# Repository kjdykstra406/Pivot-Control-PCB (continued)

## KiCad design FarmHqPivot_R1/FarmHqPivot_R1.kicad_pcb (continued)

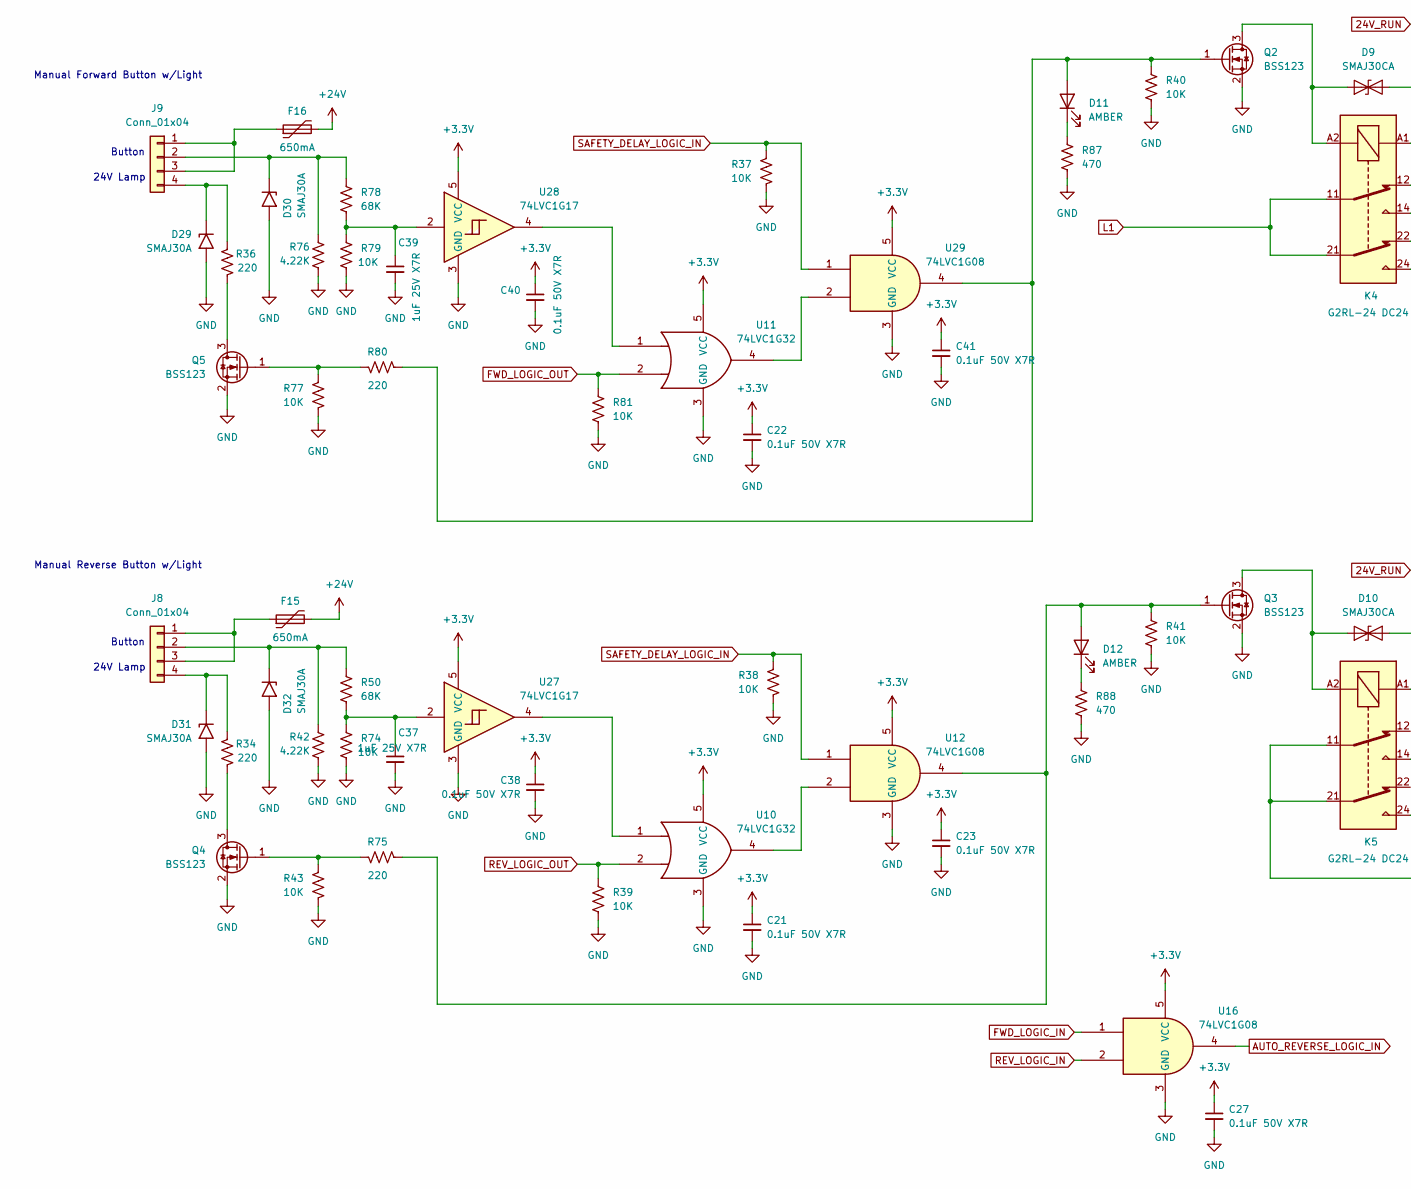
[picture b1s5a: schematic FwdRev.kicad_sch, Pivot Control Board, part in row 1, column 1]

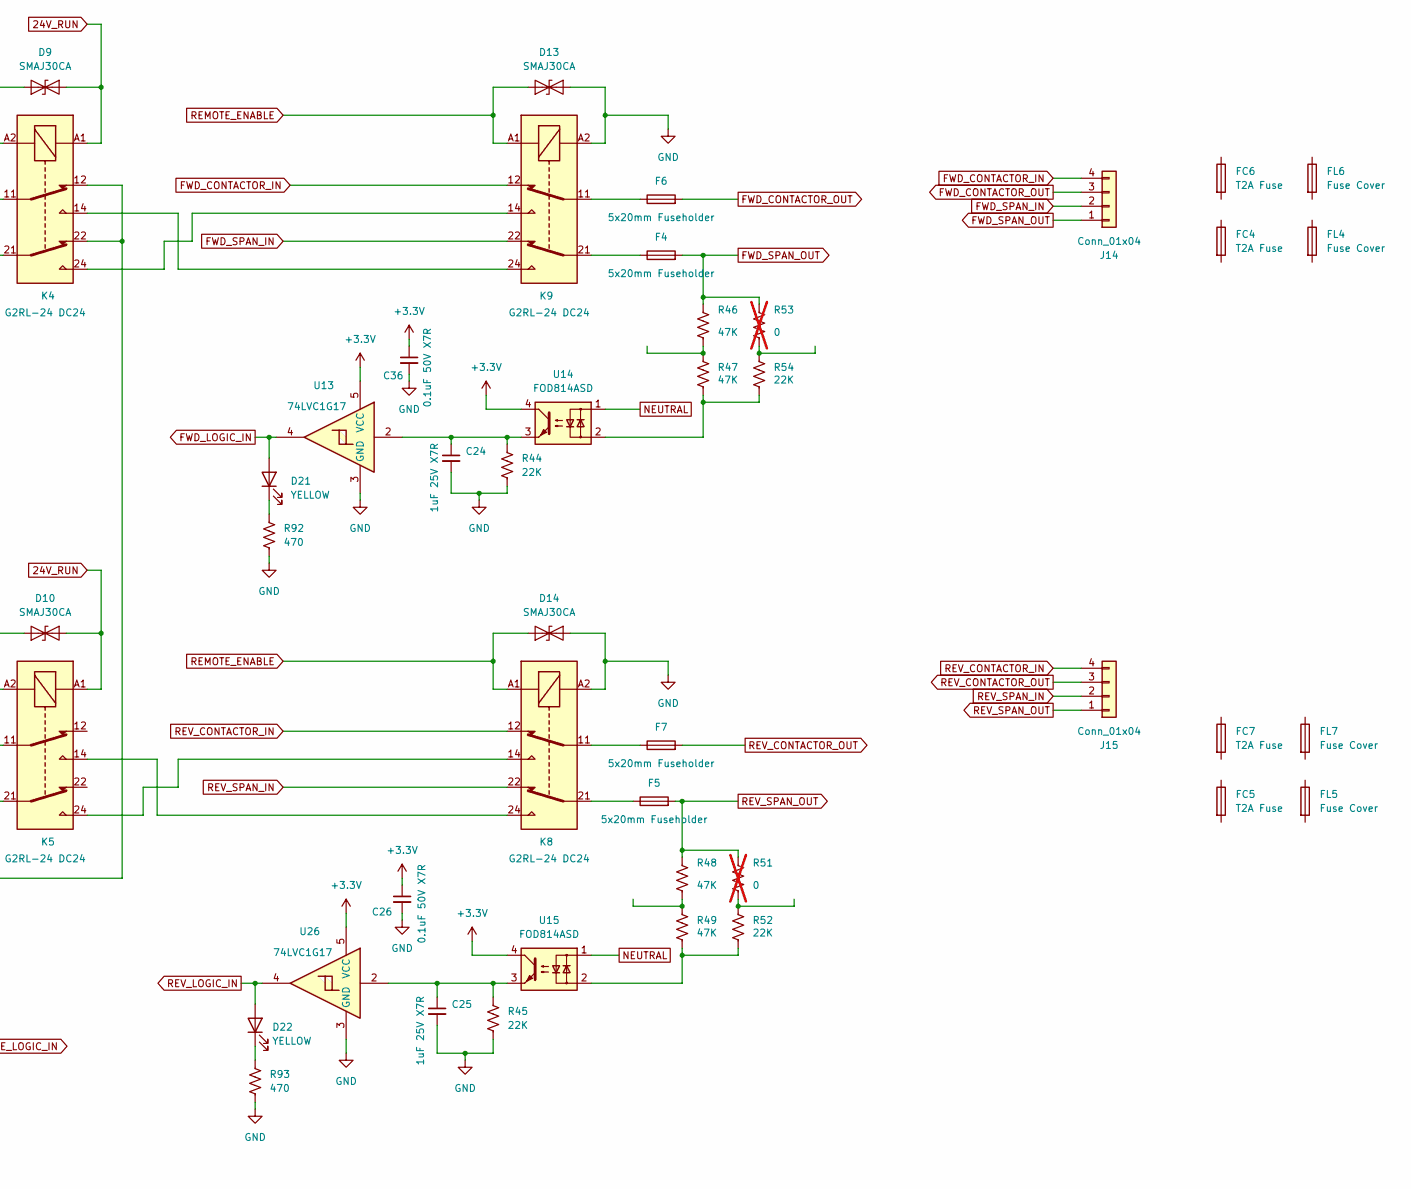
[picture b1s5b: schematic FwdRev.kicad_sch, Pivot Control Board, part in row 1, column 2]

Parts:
C21, C22, C23, C26, C27, C36, C38, C40, C41: 0.1uF 50V X7R; C_0603_1608Metric; Digikey 399-C0603C104K5RACTUDKR-ND
C24, C25, C37, C39: 1uF 25V X7R; C_0603_1608Metric; Digikey 399-C0603C105K3RACTUDKR-ND
D9, D10, D13, D14: SMAJ30CA; D_SMA; Manufacturer PN SMAJ30CA; Digikey SMAJ30CALFDKR-ND
D11, D12: AMBER; LED_0603_1608Metric; Manufacturer PN 5991030147F; Digikey 350-5991030147FDKR-ND
D21, D22: YELLOW; LED_0603_1608Metric; Manufacturer PN 5991040147F; Digikey 350-5991040147FDKR-ND
D29, D30, D31, D32: SMAJ30A; D_SMA; Manufacturer PN SMAJ30A; Digikey SMAJ30ALFDKR-ND
F4, F5, F6, F7: 5x20mm Fuseholder; 696105003002; Manufacturer PN 696105003002; Digikey 732-11373-ND
F15, F16: 650mA; Fuse_Bourns_MF-RHT100; Manufacturer PN MF-R065; Digikey MF-R065-ND
FC4, FC5, FC6, FC7: T2A Fuse; Manufacturer PN 5HT 2-R; Digikey 5923-5HT2-R-ND
FL4, FL5, FL6, FL7: Fuse Cover; Manufacturer PN 696122003001; Digikey 732-11379-ND
J8, J9: Conn_01x04; TerminalBlock_Phoenix_PT-1,5-4-3.5-H_1x04_P3.50mm_Horizontal; Manufacturer PN 1984633; Digikey 277-1860-ND
J14, J15: Conn_01x04; TerminalBlock_Phoenix_PT-1,5-4-5.0-H_1x04_P5.00mm_Horizontal; Manufacturer PN 1935187; Digikey 277-1579-ND
K4, K5, K8, K9: G2RL-24 DC24; Relay_DPDT_Finder_40.52; Manufacturer PN G2RL-24 DC24; Digikey Z148-ND
Q2, Q3, Q4, Q5: BSS123; SOT-23; Manufacturer PN BSS123; Digikey BSS123NDKR-ND
R34, R36: 220; R_1206_3216Metric; Digikey A130530DKR-ND
R37, R38, R39, R40, R41, R43, R74, R77, R79, R81: 10K; R_0603_1608Metric; Digikey 311-10KLDDKR-ND
R42, R76: 4.22K; R_2010_5025Metric; Digikey 541-4.22KACDKR-ND
R44, R45: 22K; R_0603_1608Metric; Digikey 13-RC0603FR-1322KLDKR-ND
R46, R47, R48, R49: 47K; R_2010_5025Metric; Digikey A130680DKR-ND
R50, R78: 68K; R_0603_1608Metric; Digikey 311-68.0KHRDKR-ND
R51, R53: 0; R_2010_5025Metric; Digikey YAG3380DKR-ND; not fitted
R52, R54: 22K; R_2512_6332Metric; Digikey YAG5925DKR-ND
R75, R80: 220; R_0603_1608Metric; Digikey 311-220HRDKR-ND
R87, R88, R92, R93: 470; R_0603_1608Metric; Digikey 311-470HRDKR-ND
U10, U11: 74LVC1G32; SOT-23-5; Manufacturer PN SN74LVC1G32QDBVRQ1; Digikey 296-24202-6-ND
U12, U16, U29: 74LVC1G08; SOT-23-5; Manufacturer PN SN74LVC1G08DBVR; Digikey 296-11601-6-ND
U13, U26, U27, U28: 74LVC1G17; SOT-23-5; Manufacturer PN SN74LVC1G17DBVR; Digikey 296-11933-6-ND
U14, U15: FOD814ASD; Manufacturer PN FOD814ASD; Digikey FOD814ASDDKR-ND

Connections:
24V_RUN: D9.2 (A2), D10.2 (A2), K4.A1, K5.A1; also elsewhere on the board
+3.3V: C21.1, C22.1, C23.1, C26.1, C27.1, C36.1, C38.1, C40.1, C41.1, U10.5 (VCC), U11.5 (VCC), U12.5 (VCC), U13.5 (VCC), U14.4, U15.4, U16.5 (VCC), U26.5 (VCC), U27.5 (VCC), U28.5 (VCC), U29.5 (VCC); also elsewhere on the board
+24V: F15.2, F16.2; also elsewhere on the board
AUTO_REVERSE_LOGIC_IN: U16.4; also elsewhere on the board
FWD_CONTACTOR_IN: J14.4, K9.12
FWD_CONTACTOR_OUT: F6.2, J14.3
FWD_LOGIC_IN: D21.2 (A), U13.4, U16.1; also elsewhere on the board
FWD_LOGIC_OUT: R81.1, U11.2; also elsewhere on the board
FWD_SPAN_IN: J14.2, K9.22
FWD_SPAN_OUT: F4.2, J14.1, R46.1, R53.1
GND: C21.2, C22.2, C23.2, C24.2, C25.2, C26.2, C27.2, C36.2, C37.2, C38.2, C39.2, C40.2, C41.2, D13.2 (A2), D14.2 (A2), D29.2 (A2), D30.2 (A2), D31.2 (A2), D32.2 (A2), K8.A2, K9.A2, Q2.2 (S), Q3.2 (S), Q4.2 (S), Q5.2 (S), R37.2, R38.2, R39.2, R40.2, R41.2, R42.2, R43.2, R44.2, R45.2, R74.2, R76.2, R77.2, R79.2, R81.2, R87.2, R88.2, R92.2, R93.2, U10.3 (GND), U11.3 (GND), U12.3 (GND), U13.3 (GND), U16.3 (GND), U26.3 (GND), U27.3 (GND), U28.3 (GND), U29.3 (GND); also elsewhere on the board
L1: K4.11, K4.21; also elsewhere on the board
NEUTRAL: U14.1, U15.1; also elsewhere on the board
unnamed: C24.1, R44.1, U13.2, U14.3
unnamed: C25.1, R45.1, U15.3, U26.2
unnamed: C37.1, R50.2, R74.1, U27.2
unnamed: C39.1, R78.2, R79.1, U28.2
unnamed: D9.1 (A1), K4.A2, Q2.3 (D)
unnamed: D10.1 (A1), K5.A2, Q3.3 (D)
unnamed: D11.2 (A), Q2.1 (G), R40.1, R80.2, U29.4
unnamed: D11.1 (K), R87.1
unnamed: D12.2 (A), Q3.1 (G), R41.1, R75.2, U12.4
unnamed: D12.1 (K), R88.1
unnamed: D21.1 (K), R92.1
unnamed: D22.1 (K), R93.1
unnamed: D29.1 (A1), J9.4, R36.1
unnamed: D30.1 (A1), J9.2, R76.1, R78.1
unnamed: D31.1 (A1), J8.4, R34.1
unnamed: D32.1 (A1), J8.2, R42.1, R50.1
unnamed: F4.1, K9.21
unnamed: F5.1, K8.21
unnamed: F6.1, K9.11
unnamed: F7.1, K8.11
unnamed: F15.1, J8.1, J8.3
unnamed: F16.1, J9.1, J9.3
unnamed: K4.12, K4.22, K5.11, K5.21
unnamed: K4.14, K9.24
unnamed: K4.24, K9.14
unnamed: K5.14, K8.24
unnamed: K5.24, K8.14
unnamed: Q4.3 (D), R34.2
unnamed: Q4.1 (G), R43.1, R75.1
unnamed: Q5.3 (D), R36.2
unnamed: Q5.1 (G), R77.1, R80.1
unnamed: R46.2, R47.1
unnamed: R47.2, R54.2, U14.2
unnamed: R48.2, R49.1
unnamed: R49.2, R52.2, U15.2
unnamed: R51.2, R52.1
unnamed: R53.2, R54.1
unnamed: U10.1, U27.4
unnamed: U10.4, U12.2
unnamed: U11.1, U28.4
unnamed: U11.4, U29.2
REMOTE_ENABLE: D13.1 (A1), D14.1 (A1), K8.A1, K9.A1; also elsewhere on the board
REV_CONTACTOR_IN: J15.4, K8.12
REV_CONTACTOR_OUT: F7.2, J15.3
REV_LOGIC_IN: D22.2 (A), U16.2, U26.4; also elsewhere on the board
REV_LOGIC_OUT: R39.1, U10.2; also elsewhere on the board
REV_SPAN_IN: J15.2, K8.22
REV_SPAN_OUT: F5.2, J15.1, R48.1, R51.1
SAFETY_DELAY_LOGIC_IN: R37.1, R38.1, U12.1, U29.1; also elsewhere on the board

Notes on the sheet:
24V Lamp
Manual Forward Button w/Light
Manual Reverse Button w/Light
Button

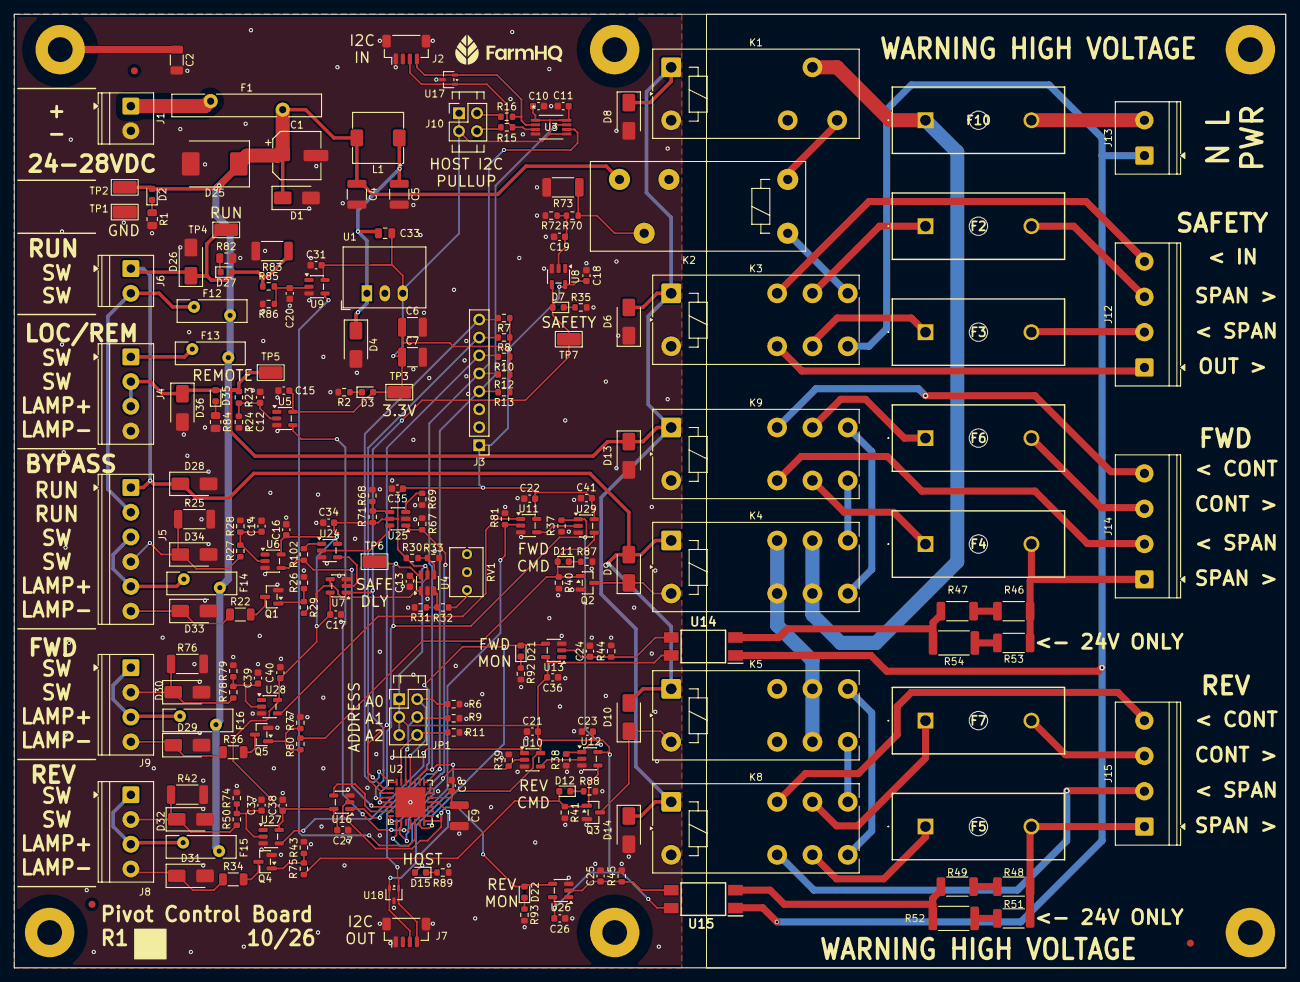
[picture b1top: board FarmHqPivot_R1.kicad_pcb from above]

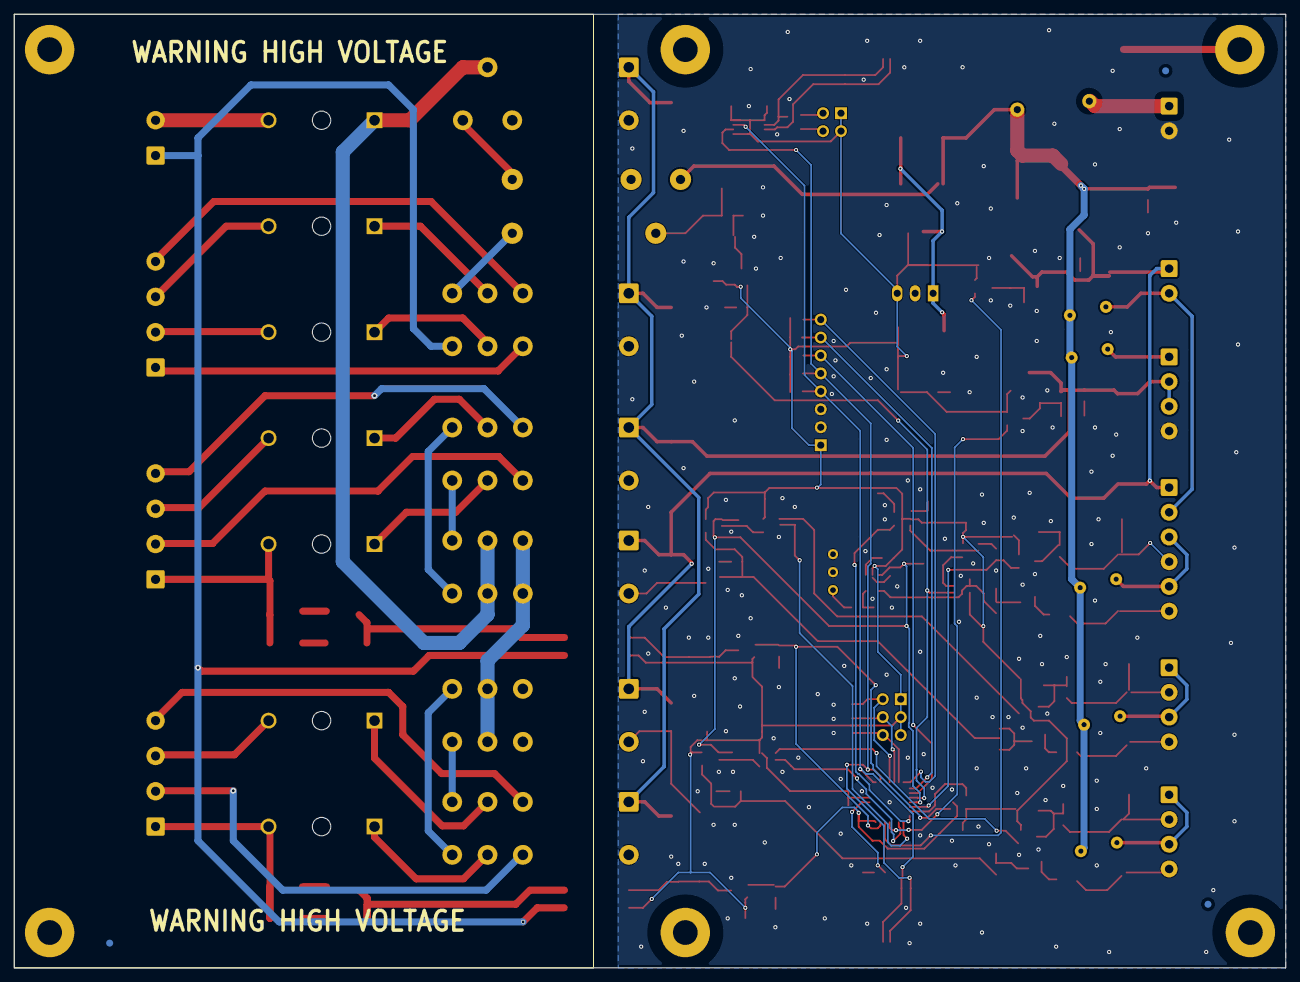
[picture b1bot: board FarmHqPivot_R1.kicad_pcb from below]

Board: 2 copper layers, 180.0 x 135.0 mm, 220 parts (3 on the bottom side), 119 nets.

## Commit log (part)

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2026-03-10 Update print statement from 'Hello' to 'Goodbye'
2026-03-11 Initial commit
    Added Controller and local remote
2026-03-17 Rough draft of PCB prototype
